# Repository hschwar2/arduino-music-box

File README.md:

# Arduino Interactive Music Box & Custom PCB Shield

A complete embedded hardware and firmware system built around the ATmega328P (Arduino Uno R3) platform. This project features a custom-designed 2-layer PCB shield, real-time song switching via dynamic loop interrupts, tone-synced 24-bit RGB lighting, diode-OR hardware logic, and dynamic potentiometer audio scaling

Designed, routed, and documented using **KiCad 9.0**.

---

## Key Technical Features

* **Custom 2-Layer PCB Shield:** Designed a custom PCB in KiCad that plugs directly onto an Arduino Uno R3, featuring optimized ground pours, clean trace routing, and through-hole component footprints.
* **Diode-OR Hardware Interrupt Circuit:** Bypasses hardware pin constraints on the ATmega328P by multiplexing 4 active-high pushbuttons into a single interrupt pin (`Digital Pin 2`) using 1N4148 switching diodes.
* **Real-Time Input Polling:** Uses analog pins (`A2–A5`) as digital inputs with 10k Ohm pull-down resistors to instantly decode button presses after triggering the ISR.
* **Dynamic Song Interruption:** Firmware regularly checks an interrupt flag during song playback loops to provide instantaneous song cancellation and input switching.
* **Tone-to-Color RGB Mapping:** Embedded C++ data structures map 27 chromatic note frequencies to 24-bit RGB values, creating custom visual lighting effects synced to audio pitch.
* **Analog Volume & Brightness Control:** Potentiometer voltage divider dynamically scales piezo speaker drive voltage and audio output levels.

---

## Hardware Architecture & Design

### Breadboard Concept

### Schematic Capture

### 3D PCB Layout

* **[View KiCad 9.0 Project Files](hardware/)**

---

## Pin Mapping & Component Specification

| Component | Arduino Pin | Circuit Function |
| :--- | :--- | :--- |
| **Diode-OR Interrupt Line** | `Digital Pin 2 (INT0)` | Common hardware interrupt trigger from all 4 buttons |
| **Blue Active LED** | `Digital Pin 6` | Status indicator (220 Ohms current limiting) |
| **Yellow Active LED** | `Digital Pin 7` | Status indicator (220 Ohms current limiting) |
| **Red Active LED** | `Digital Pin 8` | Status indicator (220 Ohms current limiting) |
| **Green Active LED** | `Digital Pin 9` | Status indicator (220 Ohms current limiting) |
| **RGB LED (Red/Green/Blue)** | `Digital Pins 11, 12, 13` | Frequency-synced chromatic lighting display |
| **Potentiometer & Buzzer** | `Analog Pin A0` | Wiper analog reference and piezo speaker driver |
| **Green Pushbutton Sense** | `Analog Pin A2` | Song 1 selection input |
| **Red Pushbutton Sense** | `Analog Pin A3` | Song 2 selection input |
| **Yellow Pushbutton Sense** | `Analog Pin A4` | Song 3 selection input |
| **Blue Pushbutton Sense** | `Analog Pin A5` | Song 4 selection input |

---

## Circuit & PCB Engineering Highlights

### Diode-OR Hardware Interrupt
Standard ATmega328P microcontrollers feature only two external hardware interrupt pins (`INT0` on Pin 2 and `INT1` on Pin 3). To handle 4 independent pushbutton inputs without continuous software polling, four 1N4148 diodes form a diode-OR logic gate:

1. Pressing any button routes current through its respective diode to pull `Digital Pin 2` `HIGH`.
2. An **Interrupt Service Routine (ISR)** triggers on the rising edge.
3. The MCU polls lines `A2–A5` to identify which specific button was pressed.

### PCB Layout Considerations
* **Board Dimensions:** Form-factor matches standard Arduino Uno R3 header dimensions ($68.6\text{ mm} \times 53.4\text{ mm}$).
* **Ground Pours:** Top and bottom layers utilize solid Ground Planes ($\text{GND}$) for return paths and noise reduction.
* **Trace Parameters:** Signal traces routed at 0.25 mm width; power rails ($5\text{V}$, $\text{GND}$) widened to 0.5 mm for power delivery.

---

## Firmware Architecture

The C++ firmware is built using custom structs that bundle note frequencies, durations, and RGB color vectors:

```cpp
struct Note {
  int frequency;  // Hz
  int duration;   // ms
  byte red;       // 0-255 PWM
  byte green;     // 0-255 PWM
  byte blue;      // 0-255 PWM
};

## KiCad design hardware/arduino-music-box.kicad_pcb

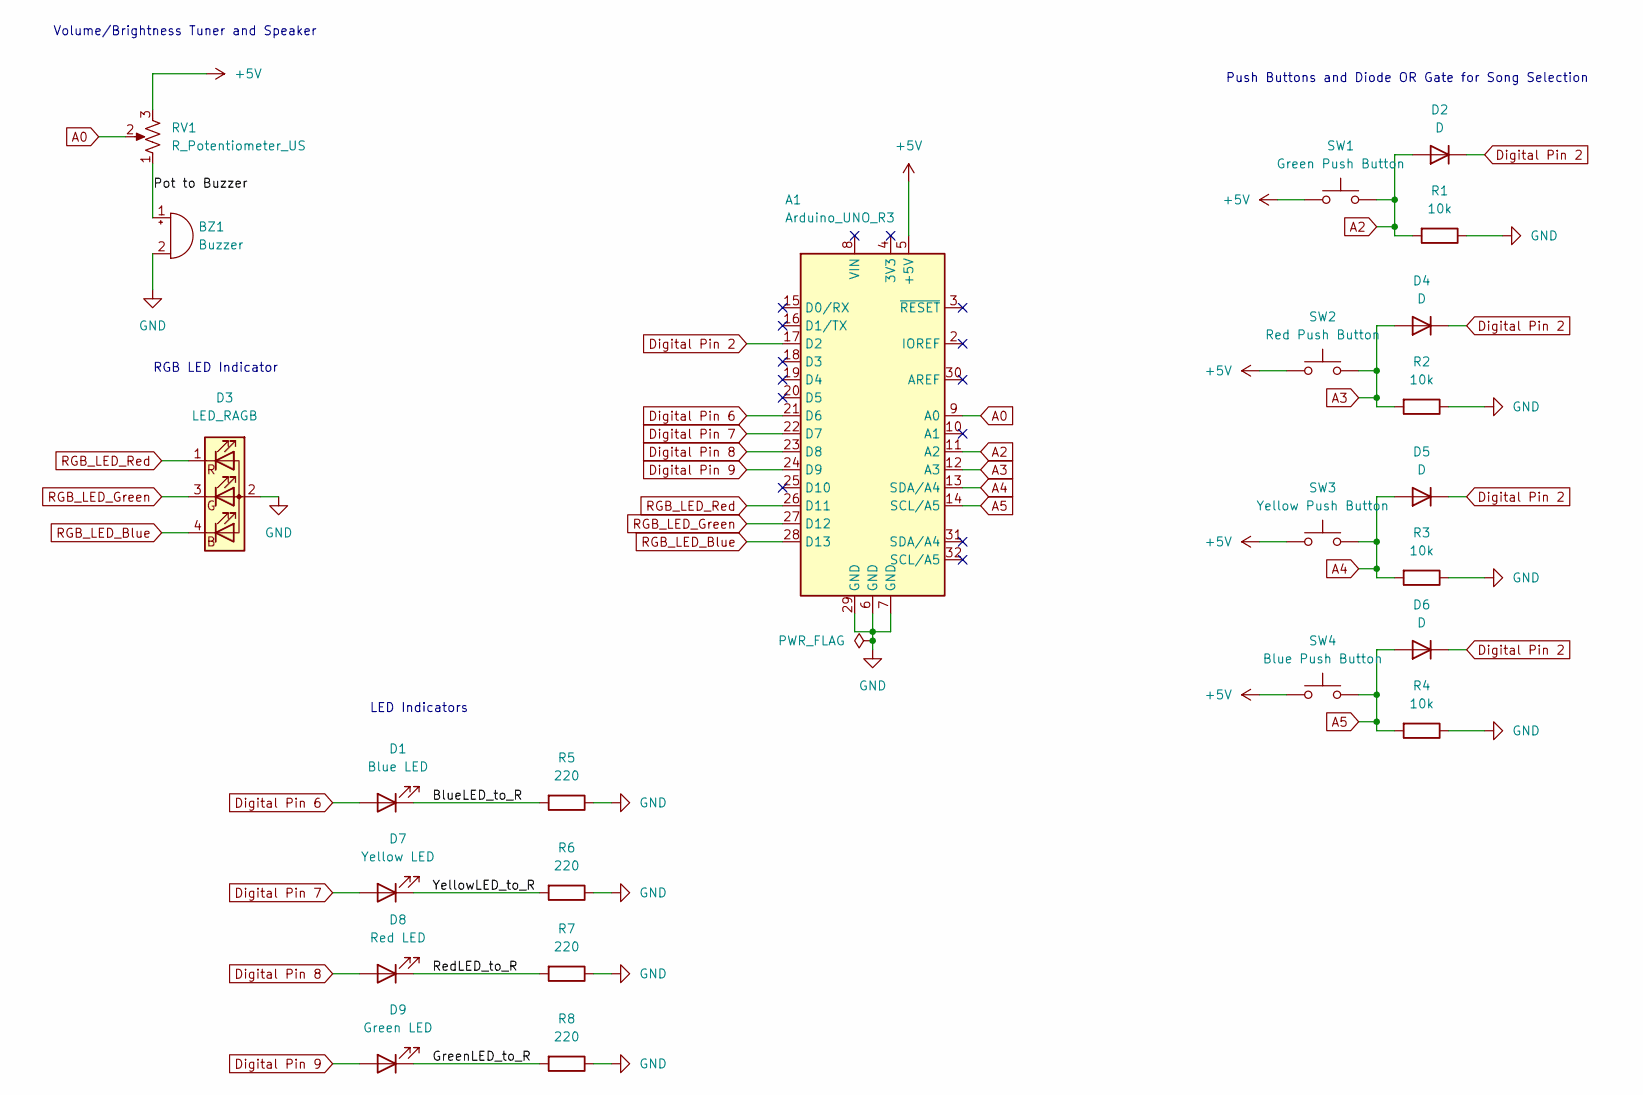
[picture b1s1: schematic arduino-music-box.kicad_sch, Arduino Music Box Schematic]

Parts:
A1: Arduino_UNO_R3
BZ1: Buzzer; Buzzer_12x9.5RM7.6
D1: Blue LED; LED_D5.0mm
D2, D4, D5, D6: D; D_DO-41_SOD81_P7.62mm_Horizontal
D3: LED_RAGB; LED_D5.0mm-4_RGB
D7: Yellow LED; LED_D5.0mm
D8: Red LED; LED_D5.0mm
D9: Green LED; LED_D5.0mm
R1, R2, R3, R4: 10k; R_Axial_DIN0207_L6.3mm_D2.5mm_P7.62mm_Horizontal
R5, R6, R7, R8: 220; R_Axial_DIN0207_L6.3mm_D2.5mm_P7.62mm_Horizontal
RV1: R_Potentiometer_US; Potentiometer_Bourns_3386P_Vertical
SW1: Green Push Button; SW_PUSH_6mm
SW2: Red Push Button; SW_PUSH_6mm
SW3: Yellow Push Button; SW_PUSH_6mm
SW4: Blue Push Button; SW_PUSH_6mm

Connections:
+5V: A1.5 (+5V), RV1.3, SW1.1, SW2.1, SW3.1, SW4.1
/BlueLED_to_R: D1.1 (K), R5.2
/GreenLED_to_R: D9.1 (K), R8.2
/Pot to Buzzer: BZ1.1 (+), RV1.1
/RedLED_to_R: D8.1 (K), R7.2
/YellowLED_to_R: D7.1 (K), R6.2
A0: A1.9 (A0), RV1.2
A2: A1.11 (A2), D2.2 (A), R1.2, SW1.2
A3: A1.12 (A3), D4.2 (A), R2.2, SW2.2
A4: A1.13 (SDA/A4), D5.2 (A), R3.2, SW3.2
A5: A1.14 (SCL/A5), D6.2 (A), R4.2, SW4.2
Digital Pin 2: A1.17 (D2), D2.1 (K), D4.1 (K), D5.1 (K), D6.1 (K)
Digital Pin 6: A1.21 (D6), D1.2 (A)
Digital Pin 7: A1.22 (D7), D7.2 (A)
Digital Pin 8: A1.23 (D8), D8.2 (A)
Digital Pin 9: A1.24 (D9), D9.2 (A)
GND: A1.6 (GND), A1.7 (GND), A1.29 (GND), BZ1.2 (-), D3.2 (A), R1.1, R2.1, R3.1, R4.1, R5.1, R6.1, R7.1, R8.1
RGB_LED_Blue: A1.28 (D13), D3.4 (BK)
RGB_LED_Green: A1.27 (D12), D3.3 (GK)
RGB_LED_Red: A1.26 (D11), D3.1 (RK)

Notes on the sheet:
RGB LED Indicator
Volume/Brightness Tuner and Speaker
Push Buttons and Diode OR Gate for Song Selection
LED Indicators

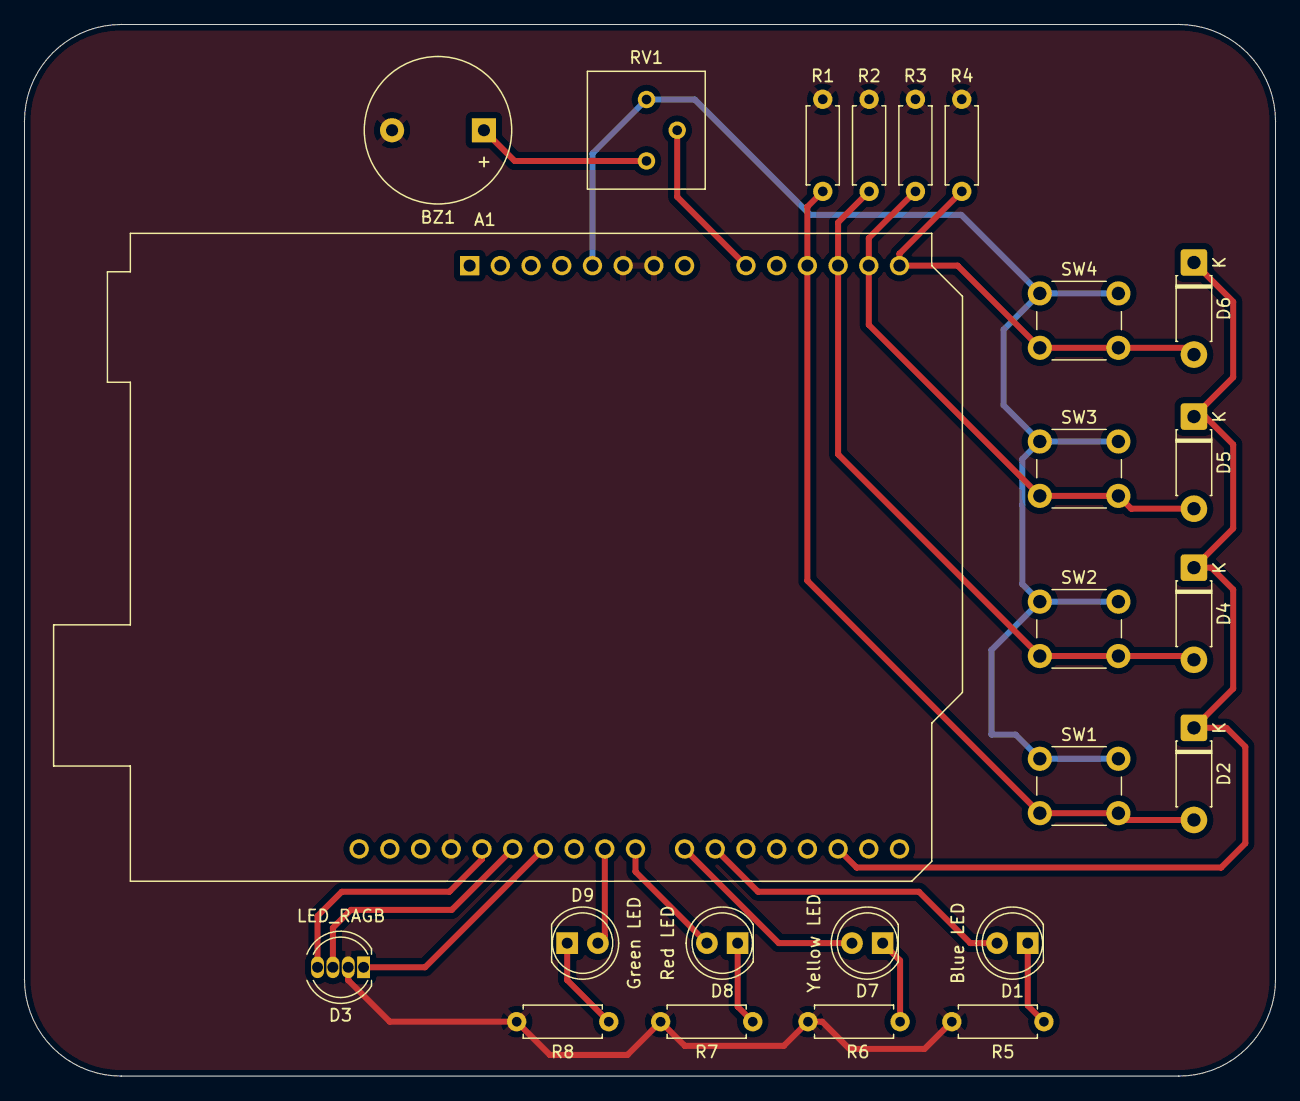
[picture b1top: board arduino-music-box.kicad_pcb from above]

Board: 2 copper layers, 103.5 x 87.0 mm, 24 parts (0 on the bottom side), 20 nets.
